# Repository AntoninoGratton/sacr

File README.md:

# sacr
Sistema de acceso controlado remotamente. Tesis

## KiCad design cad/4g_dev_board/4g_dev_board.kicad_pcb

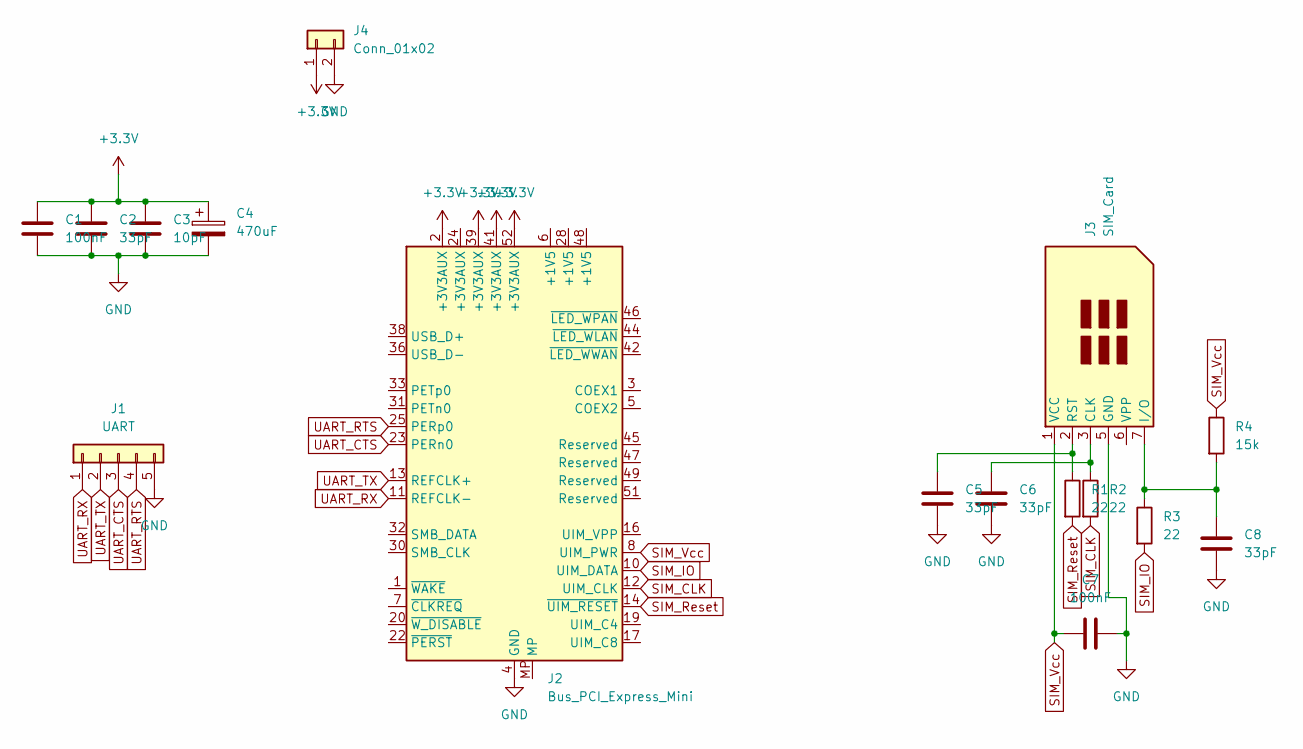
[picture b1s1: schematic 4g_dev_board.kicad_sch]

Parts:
C1, C7: 100nF; C_1206_3216Metric_Pad1.33x1.80mm_HandSolder
C2, C5, C6, C8: 33pF; C_1206_3216Metric_Pad1.33x1.80mm_HandSolder
C3: 10pF; C_1206_3216Metric_Pad1.33x1.80mm_HandSolder
C4: 470uF; CP_Radial_D10.0mm_P5.00mm
J1: UART; PinSocket_1x05_P2.54mm_Vertical
J2: Bus_PCI_Express_Mini; BUS_PCI_Express_Mini_Full
J3: SIM_Card; micro_sim
J4: Conn_01x02; TerminalBlock_bornier-2_P5.08mm
R1, R2, R3: 22; R_1206_3216Metric_Pad1.30x1.75mm_HandSolder
R4: 15k; R_1206_3216Metric_Pad1.30x1.75mm_HandSolder

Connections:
+3V3: C1.1, C2.1, C3.1, C4.1, J2.2 (+3V3AUX), J2.39 (+3V3AUX), J2.41 (+3V3AUX), J2.52 (+3V3AUX), J4.1
GND: C1.2, C2.2, C3.2, C4.2, C5.2, C6.2, C7.1, C8.2, J1.5, J2.4 (GND), J2.9 (GND), J2.15 (GND), J2.18 (GND), J2.21 (GND), J2.26 (GND), J2.27 (GND), J2.29 (GND), J2.34 (GND), J2.35 (GND), J2.37 (GND), J2.40 (GND), J2.43 (GND), J2.50 (GND), J3.5 (GND), J4.2
unnamed: C5.1, J3.2 (RST), R1.1
unnamed: C6.1, J3.3 (CLK), R2.1
unnamed: C8.1, J3.7 (I/O), R3.1, R4.2
SIM_CLK: J2.12 (UIM_CLK), R2.2
SIM_IO: J2.10 (UIM_DATA), R3.2
SIM_Reset: J2.14 (~UIM_RESET), R1.2
SIM_Vcc: C7.2, J2.8 (UIM_PWR), J3.1 (VCC), R4.1
UART_CTS: J1.3, J2.23 (PERn0)
UART_RTS: J1.4, J2.25 (PERp0)
UART_RX: J1.1, J2.11 (REFCLK-)
UART_TX: J1.2, J2.13 (REFCLK+)

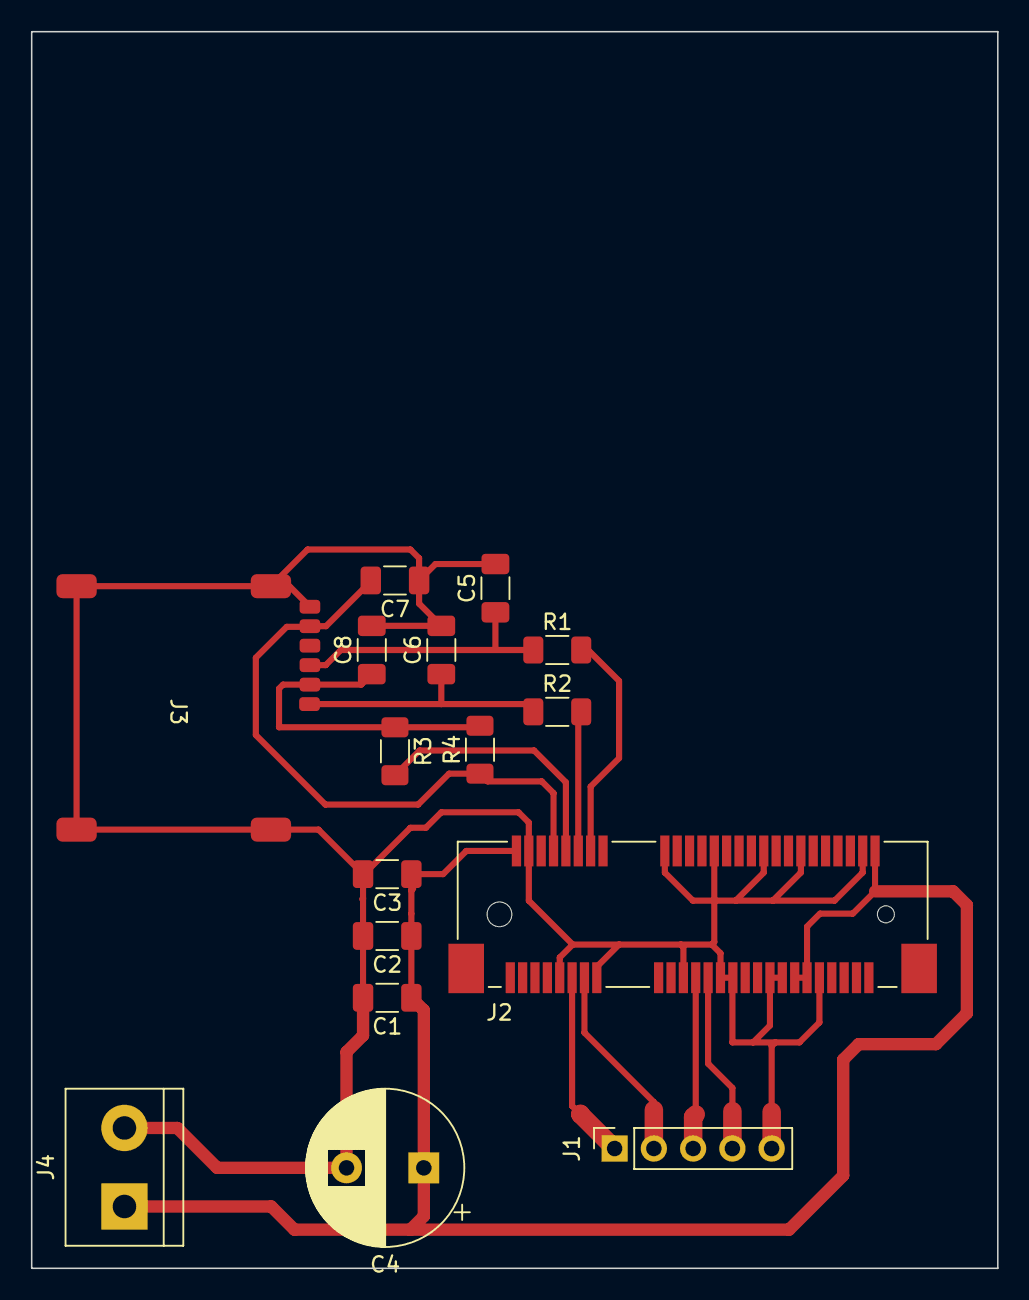
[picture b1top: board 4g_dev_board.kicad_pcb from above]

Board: 2 copper layers, 62.5 x 80.0 mm, 16 parts (0 on the bottom side), 13 nets.

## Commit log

2021-11-04 Comienzo a configurar la api del back de la tesis
2021-11-08 Agrego configuraciones para comenzar a levantar docker
2021-11-08 Agrego un sumador de onda a la pagina
2021-11-08 Agrego una estructura HTML
2021-11-09 Configuro los settings de django y la configuracion de nginx para los contenedores
2021-11-09 Agrego una funcion de ejemplo en el back
2021-11-09 Agrego el dominio a allowed hosts
2021-11-09 Creo la funcion json_response
2021-12-09 Agrego una funcion de ejemplo de posteo
2021-12-10 Corrijo un error en el backend que no dejaba funcionar el ejemplo de POST
2021-12-10 Agrego un csrf_exempt
2021-12-14 Almaceno los programas de la ESP32 en git
2021-12-15 Agrego funciones de eeprom para almacenar y levantar informacion
2021-12-16 Levanto un entorno de desarrollo para el servidor
2021-12-16 Agrego settings para produccion y para develop
2021-12-17 Elimino los pycache
2021-12-17 Corrijo el path del archivo produccion.txt que indica si se esta en produccion o en dev
2021-12-17 Corrijo un error boludo en el settings
2021-12-18 Agrego el frontend
2021-12-21 Agrego funciones para convertir bytes a enterosteros y biceversa
2021-12-22 Agrego un form de login, continuo el desarrollo. Elimino carpetas cache innecesarias
2021-12-22 Finalizo el diseño de la pantalla de login. Cambio el fondo de pantalla y agrego un spinner de cargando
2021-12-22 Agrego django axes para verificar los intentos de logueo, mitigar los ataques por fuerza bruta
2021-12-22 Logro el logueo en el back. Falta desloguear y agregar la cookie
2021-12-24 Muevo la carpeta de frontend y agrego angular a los containers
2021-12-24 No funciona bien en dev pero anda maso
2021-12-26 Agrego el deslogueo
2021-12-28 Cambio los nombres al dashboard, creo la app de alertas y agrego al settings las app
2021-12-31 Agrego la sub-app "edificios", comienzo el diagramado de las tablas de la db
2021-12-31 Agrego los models de logs y modifico el de alertas
2022-01-02 Creo las primeras migraciones de la base de datos
2022-01-02 Corrijo el diagrama de la base de datos
2022-01-04 Creo la tabla de tags y modifico la de acceso para indicar con que tag se ingreso
2022-01-10 Agrego una view en el back de logs
2022-07-20 Agrego los ultimos cambios
2022-07-20 Agrego el proyecto de kicad de la placa de desarrollo para el modulo 4g
